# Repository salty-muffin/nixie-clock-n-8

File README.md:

# nixie-clock-n-8
a nixie clock built around 4 IN-8 tubes and an INS-3 dot

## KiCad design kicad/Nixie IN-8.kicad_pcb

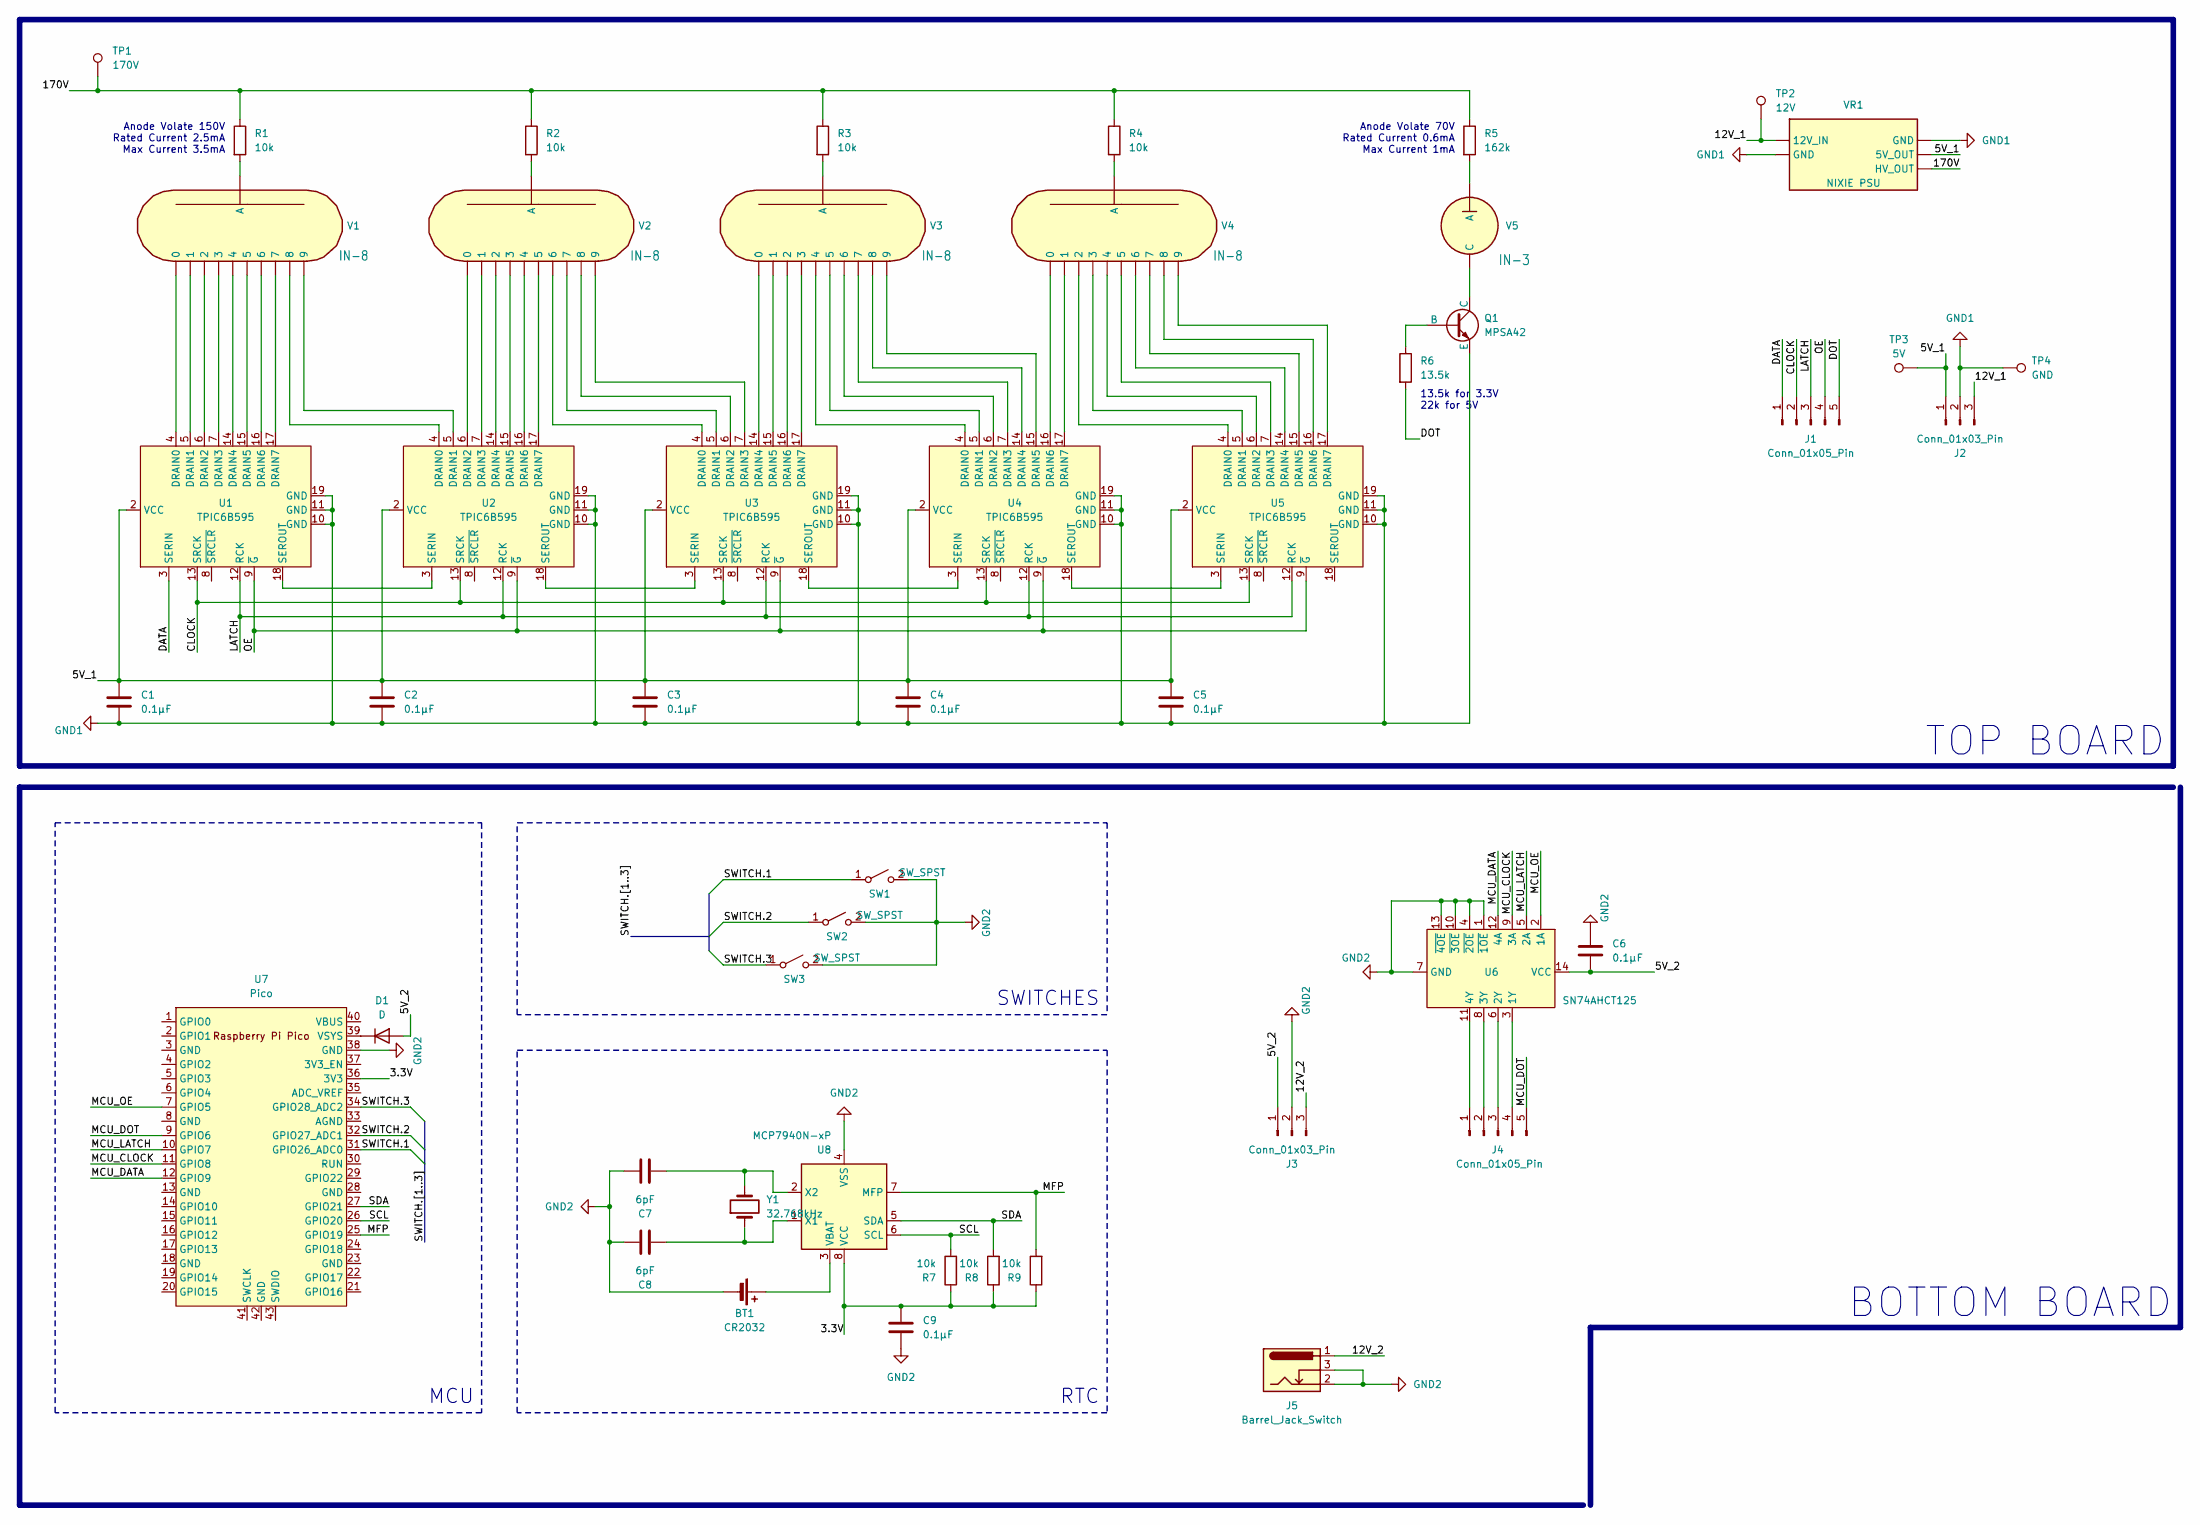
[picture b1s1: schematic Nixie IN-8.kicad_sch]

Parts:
BT1: CR2032; BatteryHolder_Keystone_3002_1x2032
C1, C2, C3, C4, C5: 0.1µF; C_Disc_D3.0mm_W1.6mm_P2.50mm
C6, C9: 0.1µF; C_1206_3216Metric_Pad1.33x1.80mm_HandSolder
C7, C8: 6pF; C_1206_3216Metric_Pad1.33x1.80mm_HandSolder
D1: D; D_SMA_Handsoldering
J1, J4: Conn_01x05_Pin; PinHeader_1x05_P2.54mm_Vertical
J2, J3: Conn_01x03_Pin; PinHeader_1x03_P2.54mm_Vertical
J5: Barrel_Jack_Switch; BarrelJack_Wuerth_6941xx301002
Q1: MPSA42; TO-92_Inline_Wide
R1, R2, R3, R4: 10k; R_Axial_DIN0207_L6.3mm_D2.5mm_P10.16mm_Horizontal
R5: 162k; R_Axial_DIN0207_L6.3mm_D2.5mm_P10.16mm_Horizontal
R6: 13.5k; R_Axial_DIN0204_L3.6mm_D1.6mm_P5.08mm_Horizontal
R7, R8, R9: 10k; R_1206_3216Metric_Pad1.30x1.75mm_HandSolder
SW1, SW2, SW3: SW_SPST; SW_Tactile_SPST_Angled_PTS645Vx83-2LFS
TP1: 170V; TestPoint_THTPad_D2.5mm_Drill1.2mm
TP2: 12V; TestPoint_THTPad_D2.5mm_Drill1.2mm
TP3: 5V; TestPoint_THTPad_D2.5mm_Drill1.2mm
TP4: GND; TestPoint_THTPad_D2.5mm_Drill1.2mm
U1, U2, U3, U4, U5: TPIC6B595; SOIC-20W_7.5x12.8mm_P1.27mm
U6: SN74AHCT125; SO-14_3.9x8.65mm_P1.27mm
U7: Pico; RPi_Pico_SMD
U8: MCP7940N-xP; SOIC-8_3.9x4.9mm_P1.27mm
V1, V2, V3, V4: IN-8
V5: IN-3; INS-3
VR1: NIXIE PSU; NIXIE-PSU-2
Y1: 32.768kHz; Crystal_DS26_D2.0mm_L6.0mm_Horizontal_SMT

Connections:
/3.3V: C9.1, R7.1, R8.1, R9.1, U7.36 (3V3), U8.8 (VCC)
/5V_1: C1.1, C2.1, C3.1, C4.1, C5.1, J2.1, TP3.1, U1.2 (VCC), U2.2 (VCC), U3.2 (VCC), U4.2 (VCC), U5.2 (VCC), VR1.5 (5V_OUT)
/5V_2: C6.2, D1.2 (A), J3.1, U6.14 (VCC)
/12V_1: J2.3, TP2.1, VR1.2 (12V_IN)
/12V_2: J3.3, J5.1
/170V: R1.1, R2.1, R3.1, R4.1, R5.1, TP1.1, VR1.3 (HV_OUT)
/CLOCK: J1.2, U1.13 (SRCK), U2.13 (SRCK), U3.13 (SRCK), U4.13 (SRCK), U5.13 (SRCK)
/DATA: J1.1, U1.3 (SERIN)
/DOT: J1.5, R6.2
/LATCH: J1.3, U1.12 (RCK), U2.12 (RCK), U3.12 (RCK), U4.12 (RCK), U5.12 (RCK)
/MCU_CLOCK: U6.9 (3A), U7.11 (GPIO8)
/MCU_DATA: U6.12 (4A), U7.12 (GPIO9)
/MCU_DOT: J4.5, U7.9 (GPIO6)
/MCU_LATCH: U6.5 (2A), U7.10 (GPIO7)
/MCU_OE: U6.2 (1A), U7.7 (GPIO5)
/MFP: R9.2, U7.25 (GPIO19), U8.7 (MFP)
/OE: J1.4, U1.9 (~G), U2.9 (~G), U3.9 (~G), U4.9 (~G), U5.9 (~G)
/SCL: R7.2, U7.26 (GPIO20), U8.6 (SCL)
/SDA: R8.2, U7.27 (GPIO21), U8.5 (SDA)
/SWITCH.1: SW1.1 (A), U7.31 (GPIO26_ADC0)
/SWITCH.2: SW2.1 (A), U7.32 (GPIO27_ADC1)
/SWITCH.3: SW3.1 (A), U7.34 (GPIO28_ADC2)
GND1: C1.2, C2.2, C3.2, C4.2, C5.2, J2.2, Q1.1 (E), TP4.1, U1.10 (GND), U1.11 (GND), U1.19 (GND), U2.10 (GND), U2.11 (GND), U2.19 (GND), U3.10 (GND), U3.11 (GND), U3.19 (GND), U4.10 (GND), U4.11 (GND), U4.19 (GND), U5.10 (GND), U5.11 (GND), U5.19 (GND), VR1.1 (GND), VR1.4 (GND)
GND2: BT1.2 (-), C6.1, C7.2, C8.2, C9.2, J3.2, J5.2, J5.3, SW1.2 (B), SW2.2 (B), SW3.2 (B), U6.1 (~1OE), U6.4 (~2OE), U6.7 (GND), U6.10 (~3OE), U6.13 (~4OE), U7.38 (GND), U8.4 (VSS)
unnamed: BT1.1 (+), U8.3 (VBAT)
unnamed: D1.1 (K), U7.39 (VSYS)
unnamed: J4.1, U6.11 (4Y)
unnamed: J4.2, U6.8 (3Y)
unnamed: J4.3, U6.6 (2Y)
unnamed: J4.4, U6.3 (1Y)
unnamed: Q1.2 (B), R6.1
unnamed: Q1.3 (C), V5.C
unnamed: R1.2, V1.A
unnamed: R2.2, V2.A
unnamed: R3.2, V3.A
unnamed: R4.2, V4.A
unnamed: R5.2, V5.A
unnamed: U1.4 (DRAIN0), V1.10 (0)
unnamed: U1.5 (DRAIN1), V1.1
unnamed: U1.6 (DRAIN2), V1.2
unnamed: U1.7 (DRAIN3), V1.3
unnamed: U1.14 (DRAIN4), V1.4
unnamed: U1.15 (DRAIN5), V1.5
unnamed: U1.16 (DRAIN6), V1.6
unnamed: U1.17 (DRAIN7), V1.7
unnamed: U1.18 (SEROUT), U2.3 (SERIN)
unnamed: U2.4 (DRAIN0), V1.8
unnamed: U2.5 (DRAIN1), V1.9
unnamed: U2.6 (DRAIN2), V2.10 (0)
unnamed: U2.7 (DRAIN3), V2.1
unnamed: U2.14 (DRAIN4), V2.2
unnamed: U2.15 (DRAIN5), V2.3
unnamed: U2.16 (DRAIN6), V2.4
unnamed: U2.17 (DRAIN7), V2.5
unnamed: U2.18 (SEROUT), U3.3 (SERIN)
unnamed: U3.4 (DRAIN0), V2.6
unnamed: U3.5 (DRAIN1), V2.7
unnamed: U3.6 (DRAIN2), V2.8
unnamed: U3.7 (DRAIN3), V2.9
unnamed: U3.14 (DRAIN4), V3.10 (0)
unnamed: U3.15 (DRAIN5), V3.1
unnamed: U3.16 (DRAIN6), V3.2
unnamed: U3.17 (DRAIN7), V3.3
unnamed: U3.18 (SEROUT), U4.3 (SERIN)
unnamed: U4.4 (DRAIN0), V3.4
unnamed: U4.5 (DRAIN1), V3.5
unnamed: U4.6 (DRAIN2), V3.6
unnamed: U4.7 (DRAIN3), V3.7
unnamed: U4.14 (DRAIN4), V3.8
unnamed: U4.15 (DRAIN5), V3.9
unnamed: U4.16 (DRAIN6), V4.10 (0)
unnamed: U4.17 (DRAIN7), V4.1
unnamed: U4.18 (SEROUT), U5.3 (SERIN)
unnamed: U5.4 (DRAIN0), V4.2
unnamed: U5.5 (DRAIN1), V4.3
unnamed: U5.6 (DRAIN2), V4.4
unnamed: U5.7 (DRAIN3), V4.5
unnamed: U5.14 (DRAIN4), V4.6
unnamed: U5.15 (DRAIN5), V4.7
unnamed: U5.16 (DRAIN6), V4.8
unnamed: U5.17 (DRAIN7), V4.9
unnamed: C8.1, U8.1 (X1), Y1.1
unnamed: C7.1, U8.2 (X2), Y1.2

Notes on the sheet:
SWITCHES
Anode Volate 150V Rated Current 2.5mA Max Current 3.5mA
13.5k for 3.3V 22k for 5V
RTC
MCU
TOP BOARD
Anode Volate 70V Rated Current 0.6mA Max Current 1mA
BOTTOM BOARD

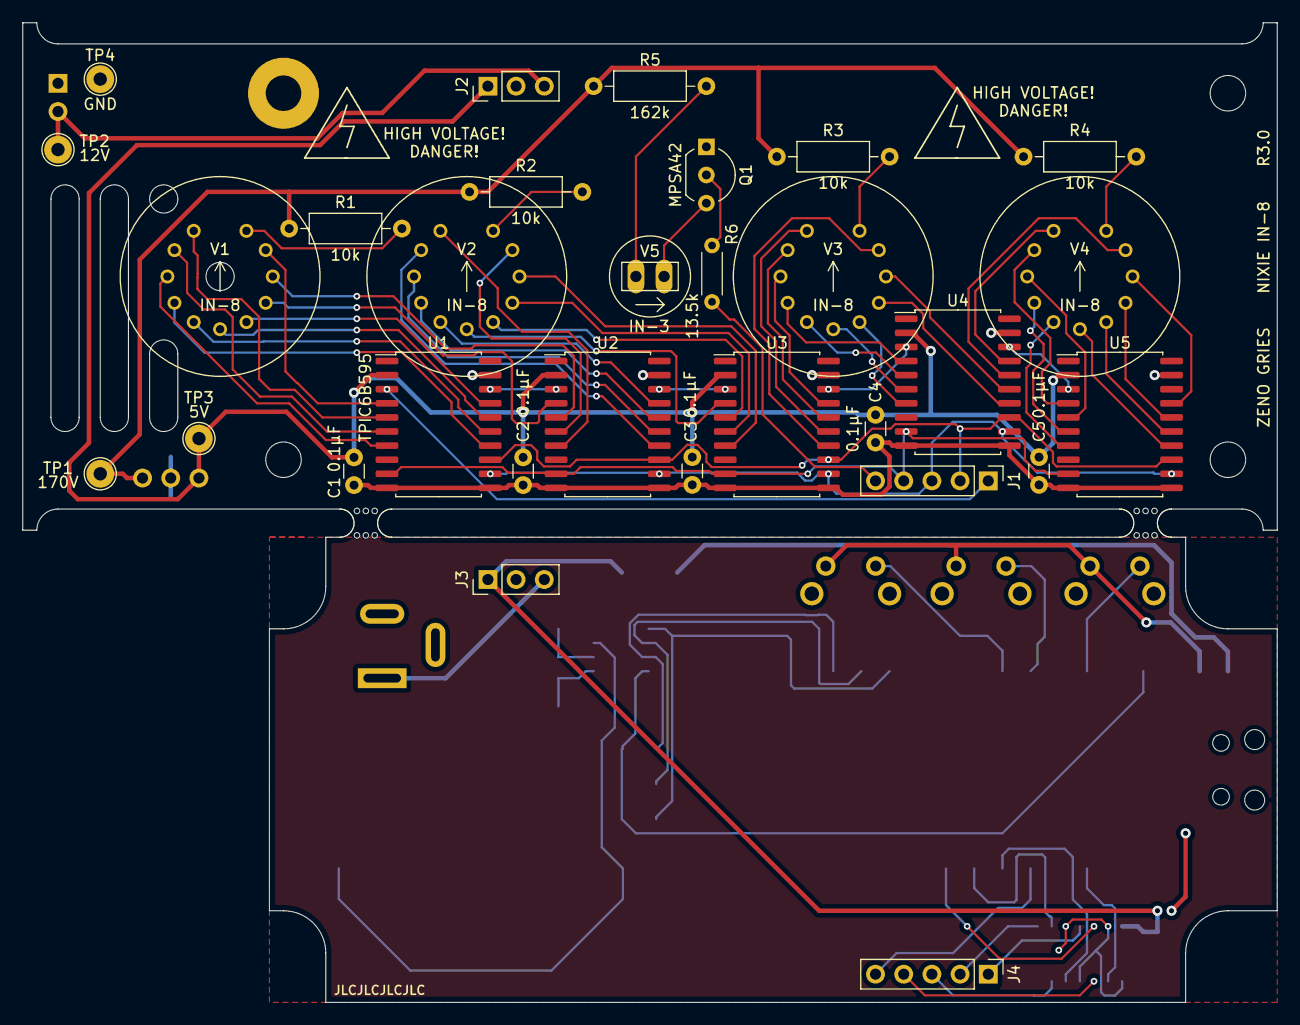
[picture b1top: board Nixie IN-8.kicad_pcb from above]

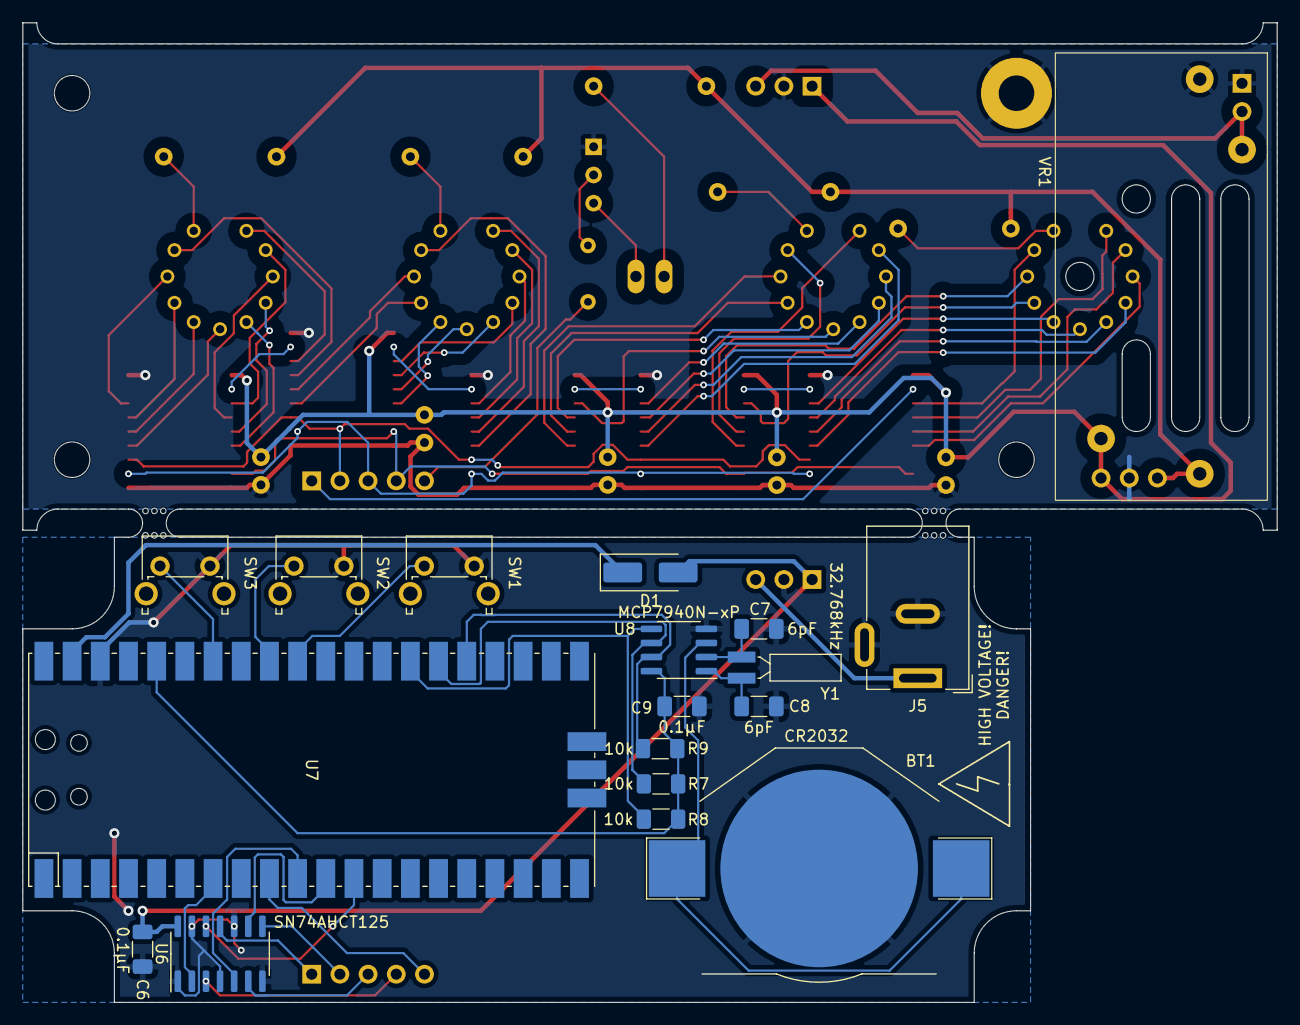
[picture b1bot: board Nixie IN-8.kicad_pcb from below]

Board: 2 copper layers, 113.0 x 88.3 mm, 50 parts (18 on the bottom side), 83 nets.

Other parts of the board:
mouse-bite-2.54mm-slot, mouse-bite-2.54mm-slot#2: VAL**; mouse-bite-2.54mm-slot

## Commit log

2019-10-23 pcbs
2019-10-23 script
2019-10-23 empty partslist added
2019-11-15 pcb updates
2019-11-16 partslists
2019-12-02 corrected pcb
2020-01-08 comoved two way buttons
2020-01-13 updated pcb and partslist
2020-01-15 updated pcb
2020-01-15 added test
2020-09-10 beauty changes
2020-11-29 new boards
2020-12-19 finished
2020-12-21 added new formfactor boards
2020-12-21 added clearance for wodden board in front of switches and jack
2023-08-29 added kicad files
2023-08-30 new design
2023-08-30 removed backups
2023-09-05 added partslist
2023-09-05 setup board
2023-09-09 finished routing
2023-09-09 added TPIC6B595
2023-09-18 started on new script
2023-09-19 finished pcb
2024-01-03 added acrylic cuts
2024-01-04 added new cuts

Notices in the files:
kicad/Nixie IN-8.kicad_pcb:
creativecommons.org
Licence: CC BY 4.0
